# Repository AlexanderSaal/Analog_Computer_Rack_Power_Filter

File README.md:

# Simple and Cost Effective Low Ripple Power Filter
---

A Ripple filter for the power supply of a modular **Analog Computer** in Eurorack format. The design goal is to be simple in part count and assembly while being cost effective and maintaining low ripple output.\
The filter is designed for a **+15V/-15V input power supply** and a **+12V/-12V output**.

The filter is devided into two parts, for the positive and negative supply voltage. In a first step the voltage is filteres in a **capacitance multiplier**, supplied by a second order **RC low-pass filter**. The output is then put through a second stage a **linear voltage regulator**. In simulations in *falstadts online circuit simulator* and *LTSpice*, the resulting output voltage should have a **voltage ripple in the lower mV range**, depending on the input powwer supply.

For an explaination on how a capacitance multiplier works, see [1].

---
## PCB render

---
## Schematic

Schematic if the power supply filter. \
As a first step the power is routed through a capacitance multiplier with a second order RC low pass filter. The corner frequency here is set to around 10 Hz.

---
## Components

**<u>Darlingtons:</u>**\
[MJF122G](https://www.digikey.de/de/products/detail/onsemi/MJF122G/919531) \
[MJF127G](https://www.digikey.de/de/products/detail/onsemi/MJF127G/919532)

**<u>Linear Regulators:</u>**\
12V 3A:\
[MIC29300-12WT](https://www.digikey.de/de/products/detail/microchip-technology/MIC29300-12WT/771587)

-12V 1.5A:\
[LM7912CT/NOPB](https://www.digikey.de/de/products/detail/texas-instruments/LM7912CT-NOPB/6355)

-12V 1.8A:\
[LM2990T-12/NOPB](https://www.digikey.de/de/products/detail/texas-instruments/LM2990T-12-NOPB/182373)

12V 1.5A:\
[LM340T-12/NOPB](https://www.digikey.de/de/products/detail/texas-instruments/LM340T-12-NOPB/6233)

**<u>TO-220 Heatsinks:</u>**\
[Boyd Laconia 513002B02500G](https://www.digikey.de/de/products/detail/boyd-laconia-llc/513002B02500G/1625590?s=N4IgTCBcDaIKwEYDMAGFYBC65oOIgF0BfIA)\
[Boyd Laconia 530002B02500G](https://www.digikey.de/de/products/detail/boyd-laconia-llc/530002B02500G/1216384)\
[Boyd Laconia 529802B02500G](https://www.digikey.de/de/products/detail/boyd-laconia-llc/529802B02500G/1216357)

**<u>Isolator:</u>**\
[THERM PAD](https://www.digikey.de/de/products/detail/boyd-laconia-llc/56-77-11G/1625385)

**<u>Screws:</u>**\
[M3,5x0,6 Nylon](https://www.digikey.de/de/products/detail/essentra-components/50M035060D012/11639017)\
[M3,5 Nut Nylon](https://www.digikey.de/de/products/detail/essentra-components/04M035060HN/9677097)

**<u>Base Power supply:</u>**\
[PD-2515](https://www.digikey.de/de/products/detail/mean-well-usa-inc/PD-2515/7705635)

**<u>Filter Capacitors:</u>**\
[UBY2A161MHL](https://www.digikey.de/de/products/detail/nichicon/UBY2A161MHL/9452708)
[0.22u CL31B224KBFNNNE](https://www.digikey.de/de/products/detail/samsung-electro-mechanics/CL31B224KBFNNNE/3886764)
[0.1u 1206B104K500CT](https://www.digikey.de/de/products/detail/walsin-technology-corporation/1206B104K500CT/9355102)

**<u>Output Linear Regulator Capacitors:</u>**\
[2.2u Typ1](https://www.digikey.de/de/products/detail/kemet/C320C225K5N5TA91707301/14318938)\
[1u Type1](https://www.digikey.de/de/products/detail/kemet/C320C105K5N5TA/14681443)\
[2.2u Type2](https://www.digikey.de/de/products/detail/tdk-corporation/FA14X7R1H225KRU06/5865806)\
[1u Type2](https://www.digikey.de/de/products/detail/tdk-corporation/FG18X5R1H105KRT06/5802871)

**<u>Filter Resistor:</u>**\
[MFR50SFTE52-100R](https://www.digikey.de/de/products/detail/yageo/MFR50SFTE52-100R/9151030)

---
## Sources

 [1] [capacitance Multiplier](https://sound-au.com/articles/cap-multiplier.htm
)

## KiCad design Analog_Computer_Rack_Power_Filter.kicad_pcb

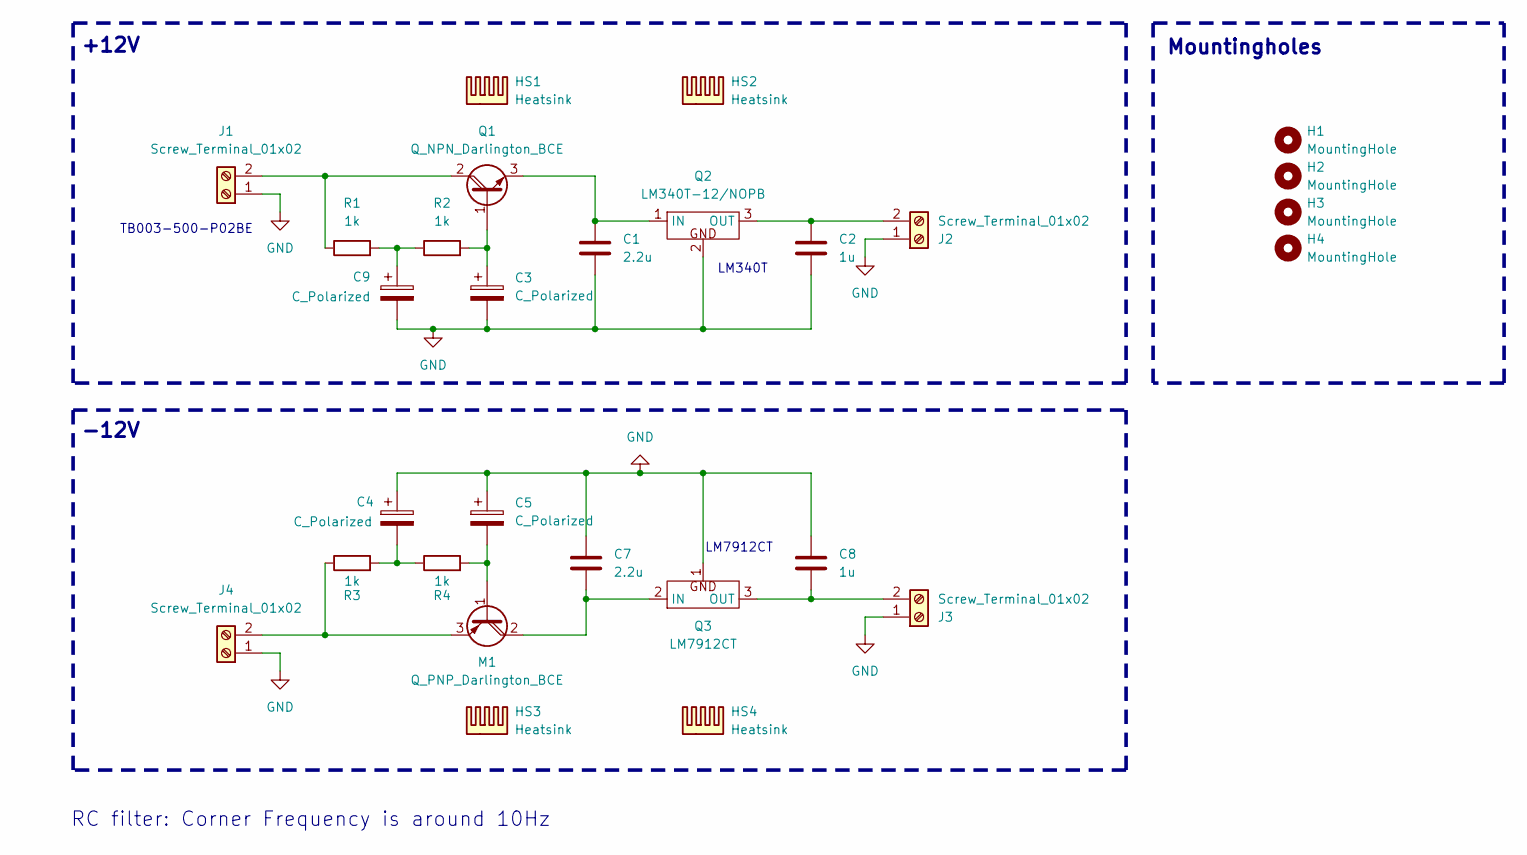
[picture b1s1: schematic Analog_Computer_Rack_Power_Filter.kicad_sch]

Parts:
C1, C7: 2.2u; C_Rect_L4.6mm_W3.0mm_P2.50mm_MKS02_FKP02
C2, C8: 1u; C_Rect_L4.6mm_W3.0mm_P2.50mm_MKS02_FKP02
C3, C4, C5, C9: C_Polarized; CP_Radial_D12.5mm_P5.00mm
H1, H2, H3, H4: MountingHole; MountingHole_3.2mm_M3_DIN965
HS1, HS2, HS3, HS4: Heatsink; Boyd Laconia, 529802B02500G, HEATSINK
J1, J2, J3, J4: Screw_Terminal_01x02; TerminalBlock_TB003-500-P02BE
M1: Q_PNP_Darlington_BCE; TO-220-3_Vertical
Q1: Q_NPN_Darlington_BCE; TO-220-3_Vertical
Q2: LM340T-12/NOPB; TO-220-3_Vertical
Q3: LM7912CT; TO-220-3_Vertical
R1, R2, R3, R4: 1k; R_Axial_DIN0207_L6.3mm_D2.5mm_P7.62mm_Horizontal

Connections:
GND: C1.2, C2.2, C3.2, C4.1, C5.1, C7.1, C8.1, C9.2, J1.1, J2.1, J3.1, J4.1, Q2.2, Q3.1
unnamed: C4.2, R3.2, R4.1
unnamed: C9.1, R1.2, R2.1
unnamed: J1.2, Q1.2 (C), R1.1
unnamed: C2.1, J2.2, Q2.3 (OUT)
unnamed: C8.2, J3.2, Q3.3 (OUT)
unnamed: J4.2, M1.3 (E), R3.1
unnamed: C5.2, M1.1 (B), R4.2
unnamed: C7.2, M1.2 (C), Q3.2 (IN)
unnamed: C3.1, Q1.1 (B), R2.2
unnamed: C1.1, Q1.3 (E), Q2.1 (IN)

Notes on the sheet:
+12V
-12V
LM7912CT
Mountingholes
RC filter: Corner Frequency is around 10Hz
LM340T
TB003-500-P02BE

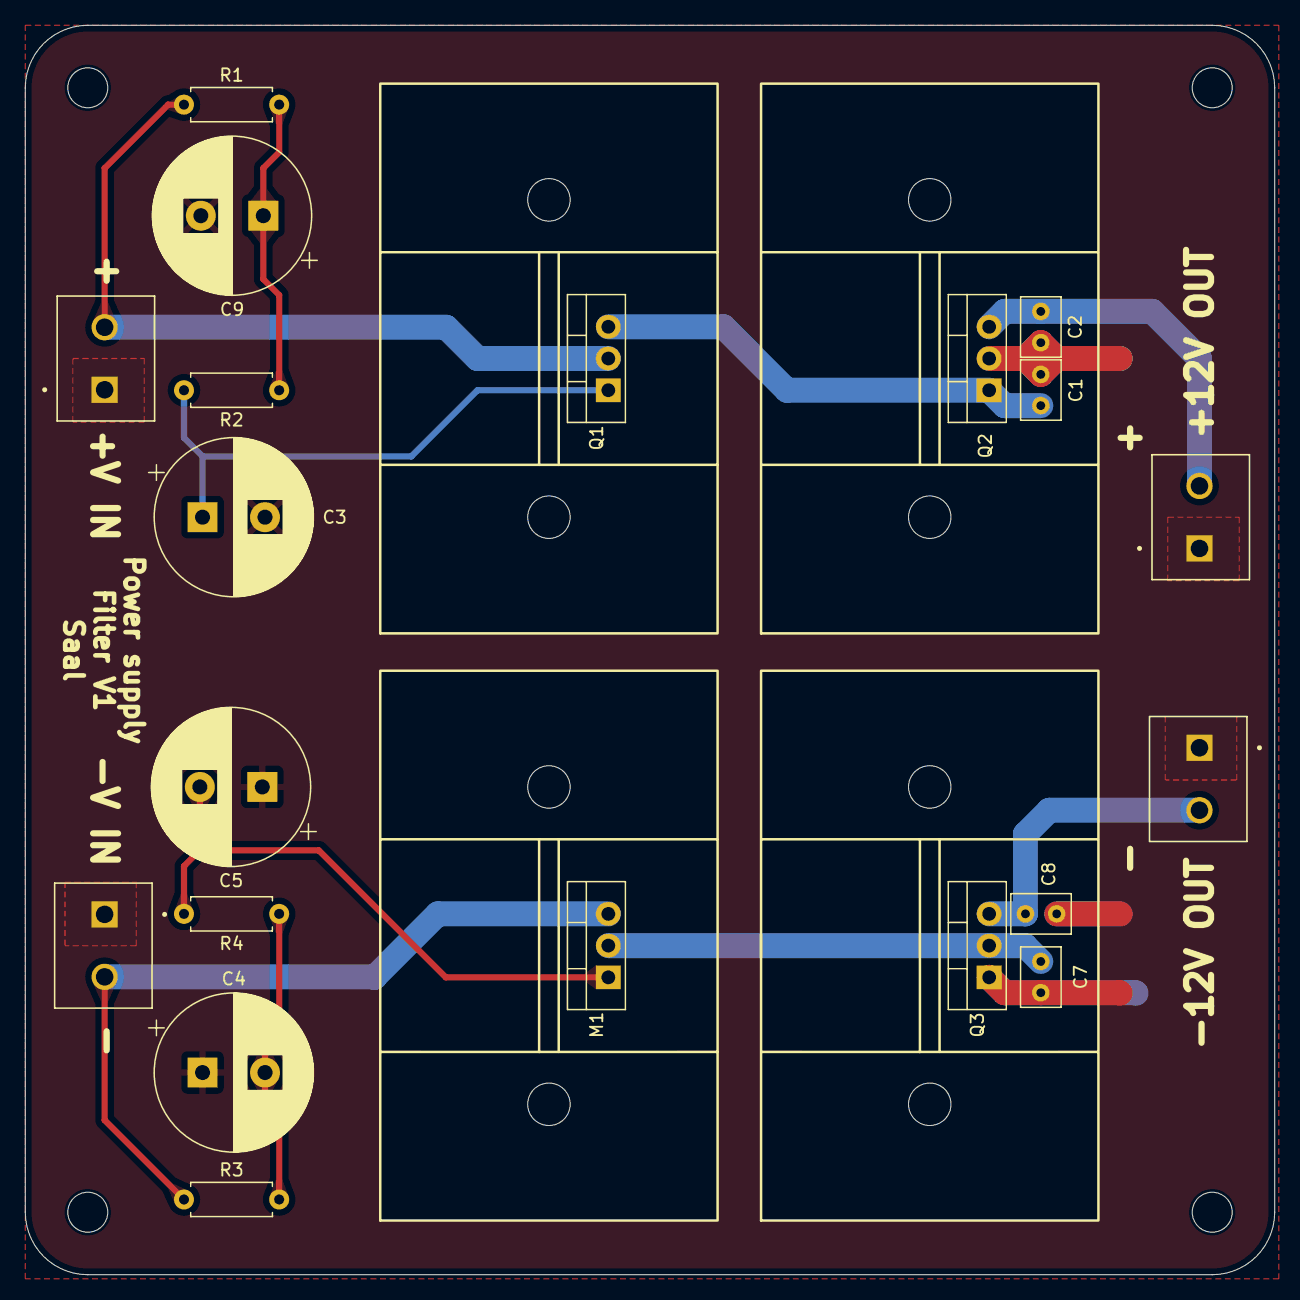
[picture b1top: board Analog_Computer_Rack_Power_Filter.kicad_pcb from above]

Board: 2 copper layers, 100.0 x 100.0 mm, 28 parts (0 on the bottom side), 11 nets.

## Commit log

2024-09-17 finished Version V1
